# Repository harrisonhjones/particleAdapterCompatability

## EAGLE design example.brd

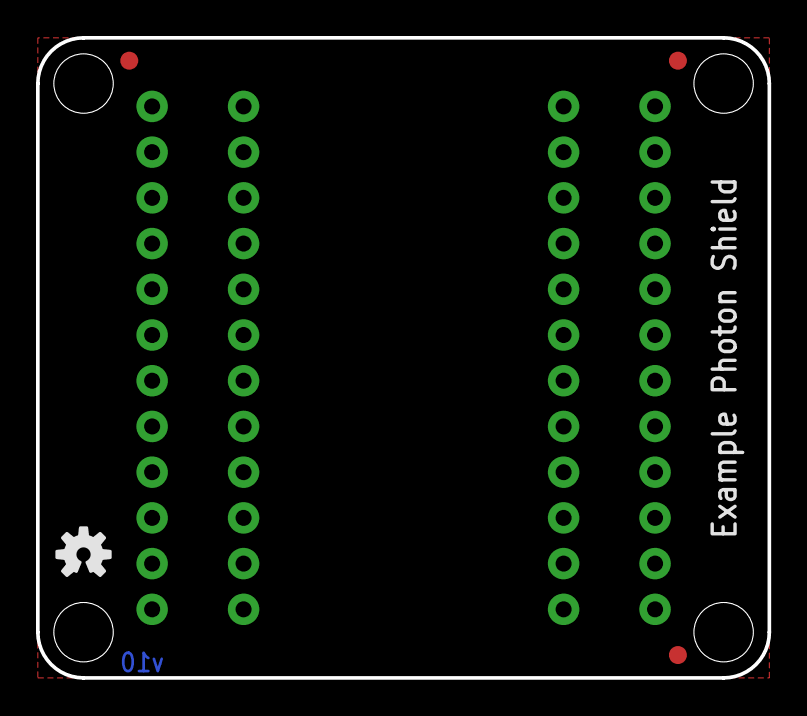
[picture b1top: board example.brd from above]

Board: 2 copper layers, 40.6 x 35.6 mm, 6 parts (0 on the bottom side), 4 nets, no tracks yet.

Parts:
FID1, FID2, FID3: FIDUCIAL1X2; FIDUCIAL-1X2
FRAME1: FRAME-LETTER; CREATIVE_COMMONS
LOGO2: OSHW-LOGOS; OSHW-LOGO-S
U$2: PARTICLE_SHIELD

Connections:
3V3: U$2.3V3_INNER, U$2.3V3_OUTER
GND: U$2.GND_1_INNER, U$2.GND_1_OUTER, U$2.GND_2_INNER, U$2.GND_2_OUTER
VBAT: U$2.VBAT_INNER, U$2.VBAT_OUTER
VIN: U$2.VIN_INNER, U$2.VIN_OUTER

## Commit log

2015-08-10 Basic configuration example
    Example "configuration" based example specifications file.
2015-08-11 Updated example with vendor info
2015-08-11 Added example flow idea
2015-08-12 Added shield library and example shield
2015-08-12 Ignoring eagle backup files
2015-08-12 Removed showing pin names for symbol. Updated example

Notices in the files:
parts and their libraries:
SparkFun-Aesthetics: Licensing: Creative Commons ShareAlike 4.0 International - https://creativecommons.org/licenses/by-sa/4.0
SparkFun-Aesthetics: Released under the Creative Commons Attribution Share-Alike 4.0 License
SparkFun-Aesthetics: https://creativecommons.org/licenses/by-sa/4.0
